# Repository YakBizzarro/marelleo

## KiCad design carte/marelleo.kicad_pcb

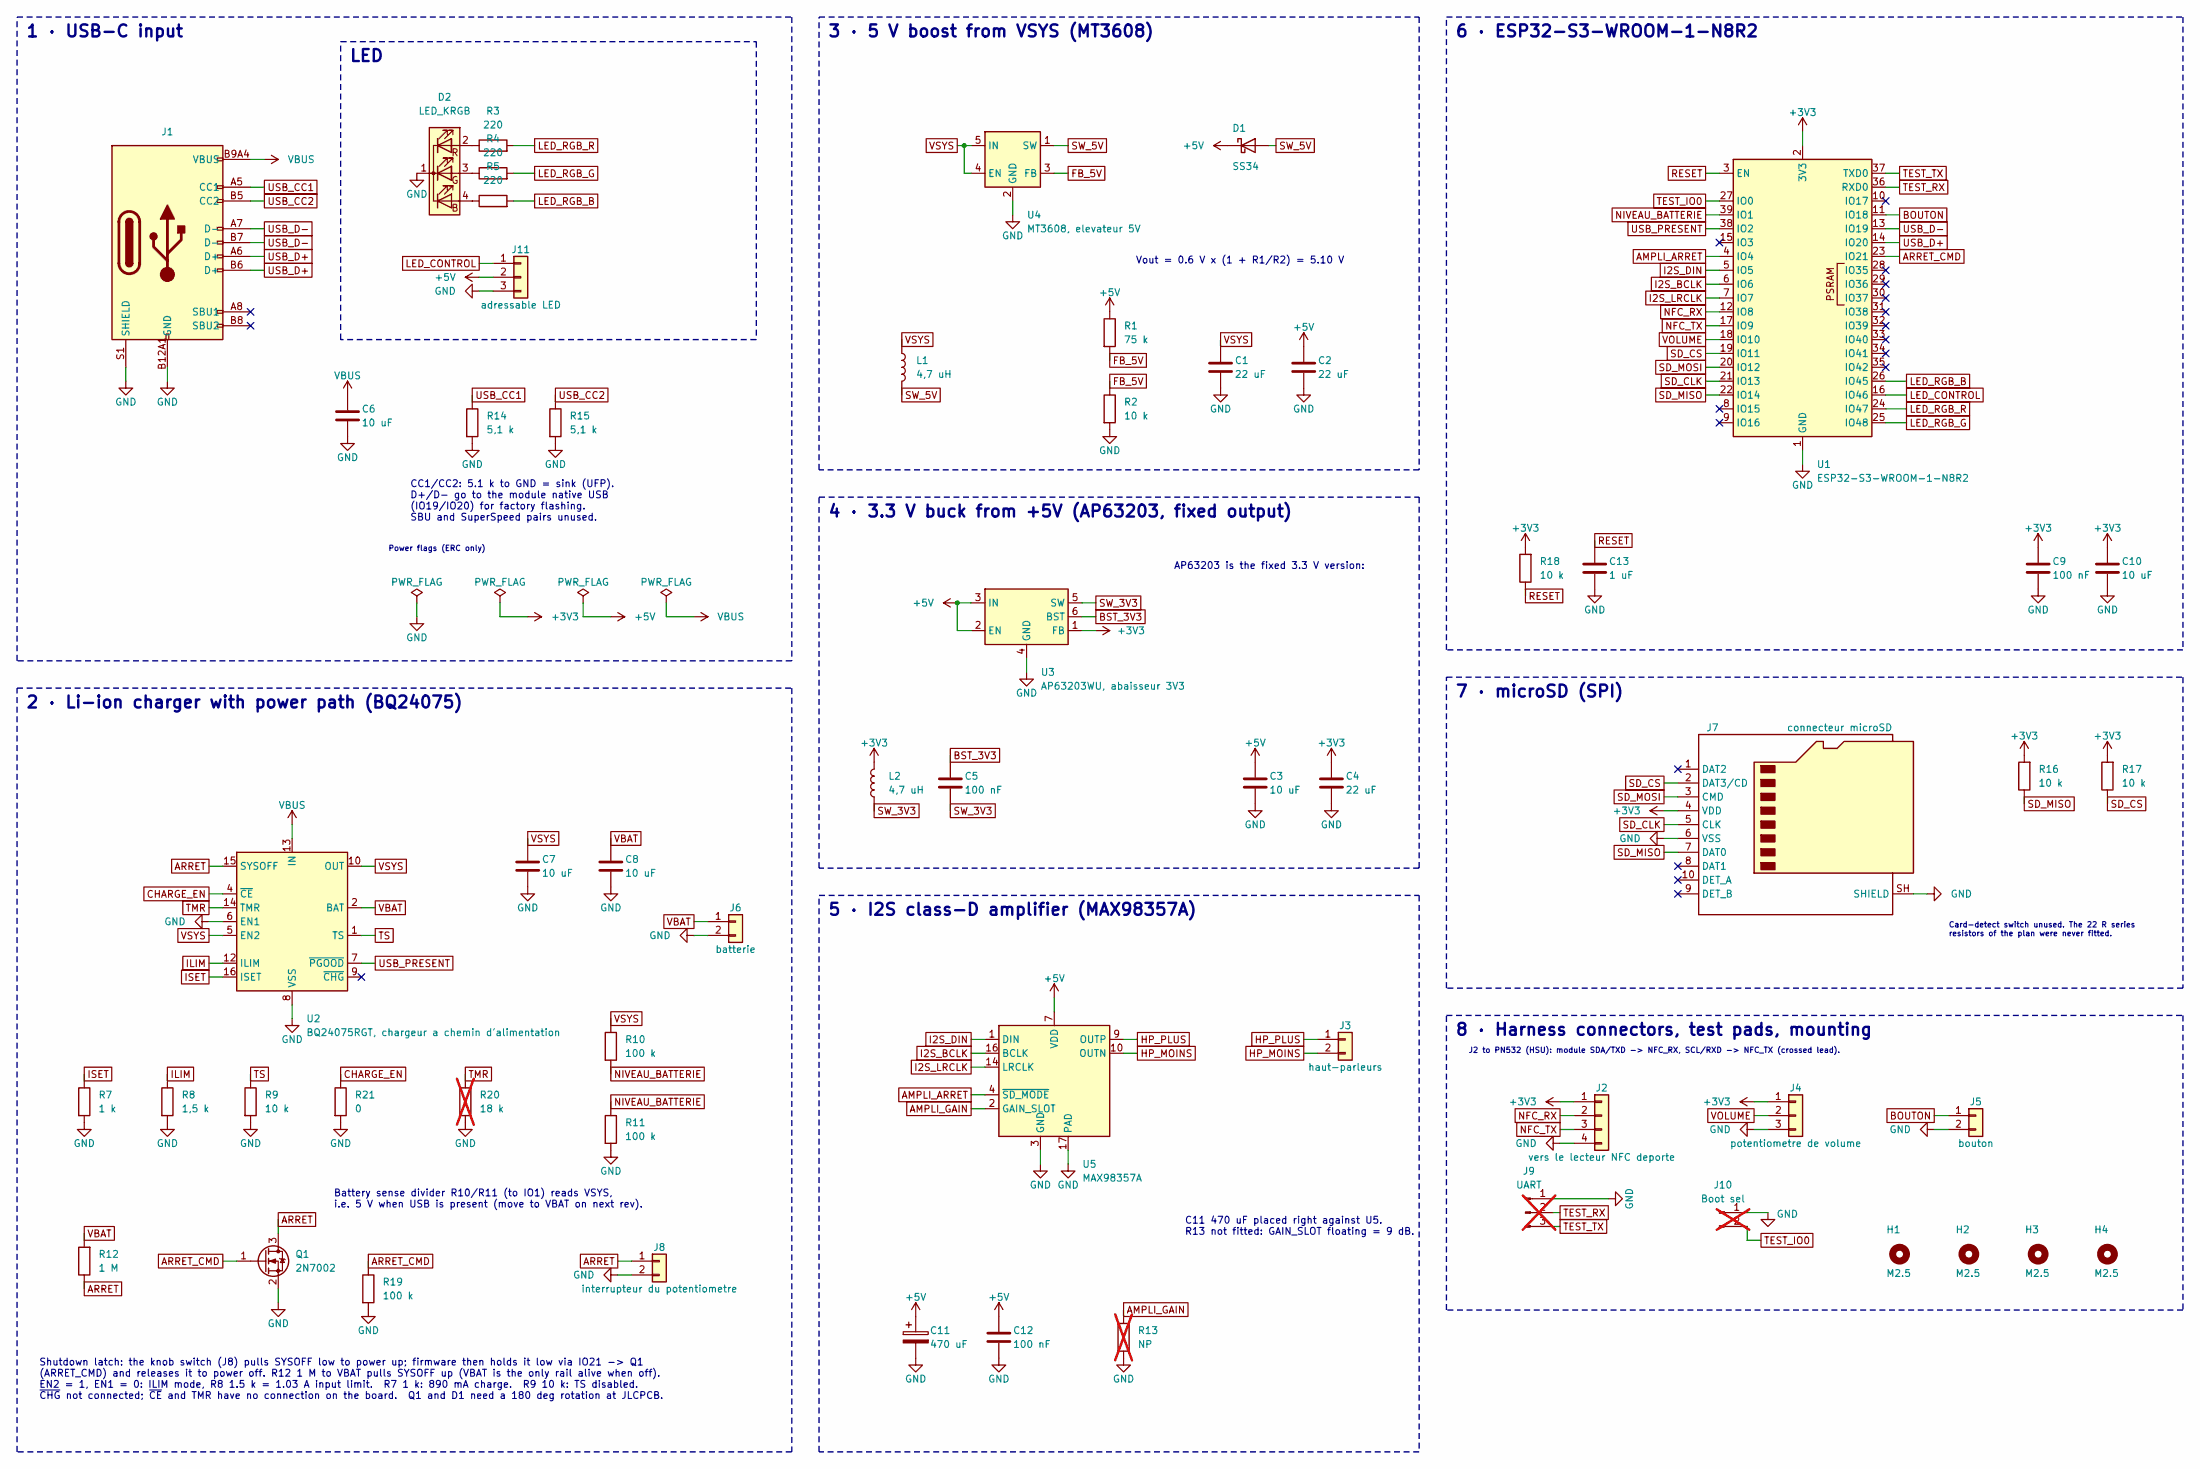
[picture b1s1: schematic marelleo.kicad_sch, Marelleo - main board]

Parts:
C1, C2, C4: 22 uF; C_0805_2012Metric; LCSC C45783
C3, C6, C7, C8, C10: 10 uF; C_0805_2012Metric; LCSC C15850
C5, C9, C12: 100 nF; C_0603_1608Metric; LCSC C14663
C11: 470 uF; CP_Elec_6.3x7.7; LCSC C82004
C13: 1 uF; C_0603_1608Metric; LCSC C15849
D1: SS34; D_SMA; LCSC C8678
D2: LED_KRGB; LED_D5.0mm-4_RGB_Wide_Pins
H1, H2, H3, H4: M2.5; MountingHole_2.7mm_M2.5
J1: Connector, USB-TYPE-C-16P; TYPE-C-SMD_HX-TYPE-C-16PIN; LCSC C2927039
J2: vers le lecteur NFC deporte; JST_PH_S4B-PH-K_1x04_P2.00mm_Horizontal; LCSC C157926
J3: haut-parleurs; JST_PH_S2B-PH-K_1x02_P2.00mm_Horizontal; LCSC C173752
J4: potentiometre de volume; JST_PH_S3B-PH-K_1x03_P2.00mm_Horizontal; LCSC C157929
J5: bouton; JST_PH_S2B-PH-K_1x02_P2.00mm_Horizontal; LCSC C173752
J6: batterie; JST_PH_S2B-PH-K_1x02_P2.00mm_Horizontal; LCSC C173752
J7: connecteur microSD; microSD_HC_Hirose_DM3AT-SF-PEJM5; LCSC C114218
J8: interrupteur du potentiometre; JST_PH_S2B-PH-K_1x02_P2.00mm_Horizontal; LCSC C173752
J9: UART; PinHeader_1x03_P2.54mm_Vertical; not fitted
J10: Boot sel; PinHeader_1x02_P2.54mm_Vertical; not fitted
J11: adressable LED; JST_PH_S3B-PH-K_1x03_P2.00mm_Horizontal; LCSC C157929
L1, L2: 4,7 uH; L_Taiyo-Yuden_MD-4040; LCSC C206284
Q1: 2N7002; SOT-23; LCSC C8545
R1: 75 k; R_0603_1608Metric; LCSC C23242
R2, R9, R16, R17, R18: 10 k; R_0603_1608Metric; LCSC C25804
R3, R4, R5: 220; R_0603_1608Metric
R7: 1 k; R_0603_1608Metric; LCSC C21190
R8: 1,5 k; R_0603_1608Metric; LCSC C22843
R10, R11, R19: 100 k; R_0603_1608Metric; LCSC C25803
R12: 1 M; R_0603_1608Metric; LCSC C22935
R13: NP; R_0603_1608Metric; not fitted
R14, R15: 5,1 k; R_0603_1608Metric; LCSC C23186
R20: 18 k; R_0603_1608Metric; LCSC C25804; not fitted
R21: 0; R_0603_1608Metric; LCSC C25804
U1: ESP32-S3-WROOM-1-N8R2; ESP32-S3-WROOM-1; LCSC C2913204
U2: BQ24075RGT, chargeur a chemin d'alimentation; VQFN-16-1EP_3x3mm_P0.5mm_EP1.1x1.1mm; LCSC C15464
U3: AP63203WU, abaisseur 3V3; TSOT-23-6; LCSC C780769
U4: MT3608, elevateur 5V; SOT-23-6; LCSC C84817
U5: MAX98357A; TQFN-16-1EP_3x3mm_P0.5mm_EP1.23x1.23mm; LCSC C910544

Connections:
+3V3: C4.1, C9.1, C10.1, J2.1, J4.1, J7.4 (VDD), L2.2, R16.2, R17.2, R18.2, U1.2 (3V3), U3.1 (FB)
+5V: C2.1, C3.1, C11.1, C12.1, D1.1 (K), J11.2, R1.1, U3.2 (EN), U3.3 (IN), U5.7 (VDD), U5.8 (VDD)
AMPLI_ARRET: U1.4 (IO4), U5.4 (~SD_MODE)
AMPLI_GAIN: R13.1, U5.2 (GAIN_SLOT)
ARRET: J8.1, Q1.3 (D), R12.1, U2.15 (SYSOFF)
ARRET_CMD: Q1.1 (G), R19.1, U1.23 (IO21)
BOUTON: J5.1, U1.11 (IO18)
BST_3V3: C5.1, U3.6 (BST)
CHARGE_EN: R21.1, U2.4 (~CE)
FB_5V: R1.2, R2.1, U4.3 (FB)
GND: C1.2, C2.2, C3.2, C4.2, C6.2, C7.2, C8.2, C9.2, C10.2, C11.2, C12.2, C13.2, D2.1 (K), J1.A12B1 (GND), J1.B12A1 (GND), J1.S1 (SHIELD), J2.4, J4.3, J5.2, J6.2, J7.6 (VSS), J7.SH (SHIELD), J8.2, J9.1, J10.1, J11.3, Q1.2 (S), R2.2, R7.2, R8.2, R9.2, R11.2, R13.2, R14.2, R15.2, R19.2, R20.2, R21.2, U1.1 (GND), U1.40 (GND), U1.41 (GND), U2.6 (EN1), U2.8 (VSS), U2.17 (VSS), U3.4 (GND), U4.2 (GND), U5.3 (GND), U5.11 (GND), U5.15 (GND), U5.17 (PAD)
HP_MOINS: J3.2, U5.10 (OUTN)
HP_PLUS: J3.1, U5.9 (OUTP)
I2S_BCLK: U1.6 (IO6), U5.16 (BCLK)
I2S_DIN: U1.5 (IO5), U5.1 (DIN)
I2S_LRCLK: U1.7 (IO7), U5.14 (LRCLK)
ILIM: R8.1, U2.12 (ILIM)
ISET: R7.1, U2.16 (ISET)
LED_CONTROL: J11.1, U1.16 (IO46)
LED_RGB_B: R5.2, U1.26 (IO45)
LED_RGB_G: R4.2, U1.25 (IO48)
LED_RGB_R: R3.2, U1.24 (IO47)
NFC_RX: J2.2, U1.12 (IO8)
NFC_TX: J2.3, U1.17 (IO9)
NIVEAU_BATTERIE: R10.2, R11.1, U1.39 (IO1)
unnamed: D2.4 (BA), R5.1
unnamed: D2.3 (GA), R4.1
unnamed: D2.2 (RA), R3.1
RESET: C13.1, R18.1, U1.3 (EN)
SD_CLK: J7.5 (CLK), U1.21 (IO13)
SD_CS: J7.2 (DAT3/CD), R17.1, U1.19 (IO11)
SD_MISO: J7.7 (DAT0), R16.1, U1.22 (IO14)
SD_MOSI: J7.3 (CMD), U1.20 (IO12)
SW_3V3: C5.2, L2.1, U3.5 (SW)
SW_5V: D1.2 (A), L1.2, U4.1 (SW)
TEST_IO0: J10.2, U1.27 (IO0)
TEST_RX: J9.2, U1.36 (RXD0)
TEST_TX: J9.3, U1.37 (TXD0)
TMR: R20.1, U2.14 (TMR)
TS: R9.1, U2.1 (TS)
USB_CC1: J1.A5 (CC1), R14.1
USB_CC2: J1.B5 (CC2), R15.1
USB_D+: J1.A6 (D+), J1.B6 (D+), U1.14 (IO20)
USB_D-: J1.A7 (D-), J1.B7 (D-), U1.13 (IO19)
USB_PRESENT: U1.38 (IO2), U2.7 (~PGOOD)
VBAT: C8.1, J6.1, R12.2, U2.2 (BAT), U2.3 (BAT)
VBUS: C6.1, J1.A9B4 (VBUS), J1.B9A4 (VBUS), U2.13 (IN)
VOLUME: J4.2, U1.18 (IO10)
VSYS: C1.1, C7.1, L1.1, R10.1, U2.5 (EN2), U2.10 (OUT), U2.11 (OUT), U4.4 (EN), U4.5 (IN)

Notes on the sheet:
Battery sense divider R10/R11 (to IO1) reads VSYS, i.e. 5 V when USB is present (move to VBAT on next rev).
Shutdown latch: the knob switch (J8) pulls SYSOFF low to power up; firmware then holds it low via IO21 -> Q1 (ARRET_CMD) and releases it to power off. R12 1 M to VBAT pulls SYSOFF up (VBAT is the only rail alive when off). EN2 = 1, EN1 = 0: ILIM mode, R8 1.5 k = 1.03 A input limit. R7 1 k: 890 mA c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
Card-detect switch unused. The 22 R series resistors of the plan were never fitted.
4 · 3.3 V buck from +5V (AP63203, fixed output)
1 · USB-C input
AP63203 is the fixed 3.3 V version:
3 · 5 V boost from VSYS (MT3608)
CC1/CC2: 5.1 k to GND = sink (UFP). D+/D- go to the module native USB (IO19/IO20) for factory flashing. SBU and SuperSpeed pairs unused.
Power flags (ERC only)
5 · I2S class-D amplifier (MAX98357A)
J2 to PN532 (HSU): module SDA/TXD -> NFC_RX, SCL/RXD -> NFC_TX (crossed lead).
LED
Vout = 0.6 V x (1 + R1/R2) = 5.10 V
6 · ESP32-S3-WROOM-1-N8R2
7 · microSD (SPI)
2 · Li-ion charger with power path (BQ24075)
C11 470 uF placed right against U5. R13 not fitted: GAIN_SLOT floating = 9 dB.
8 · Harness connectors, test pads, mounting

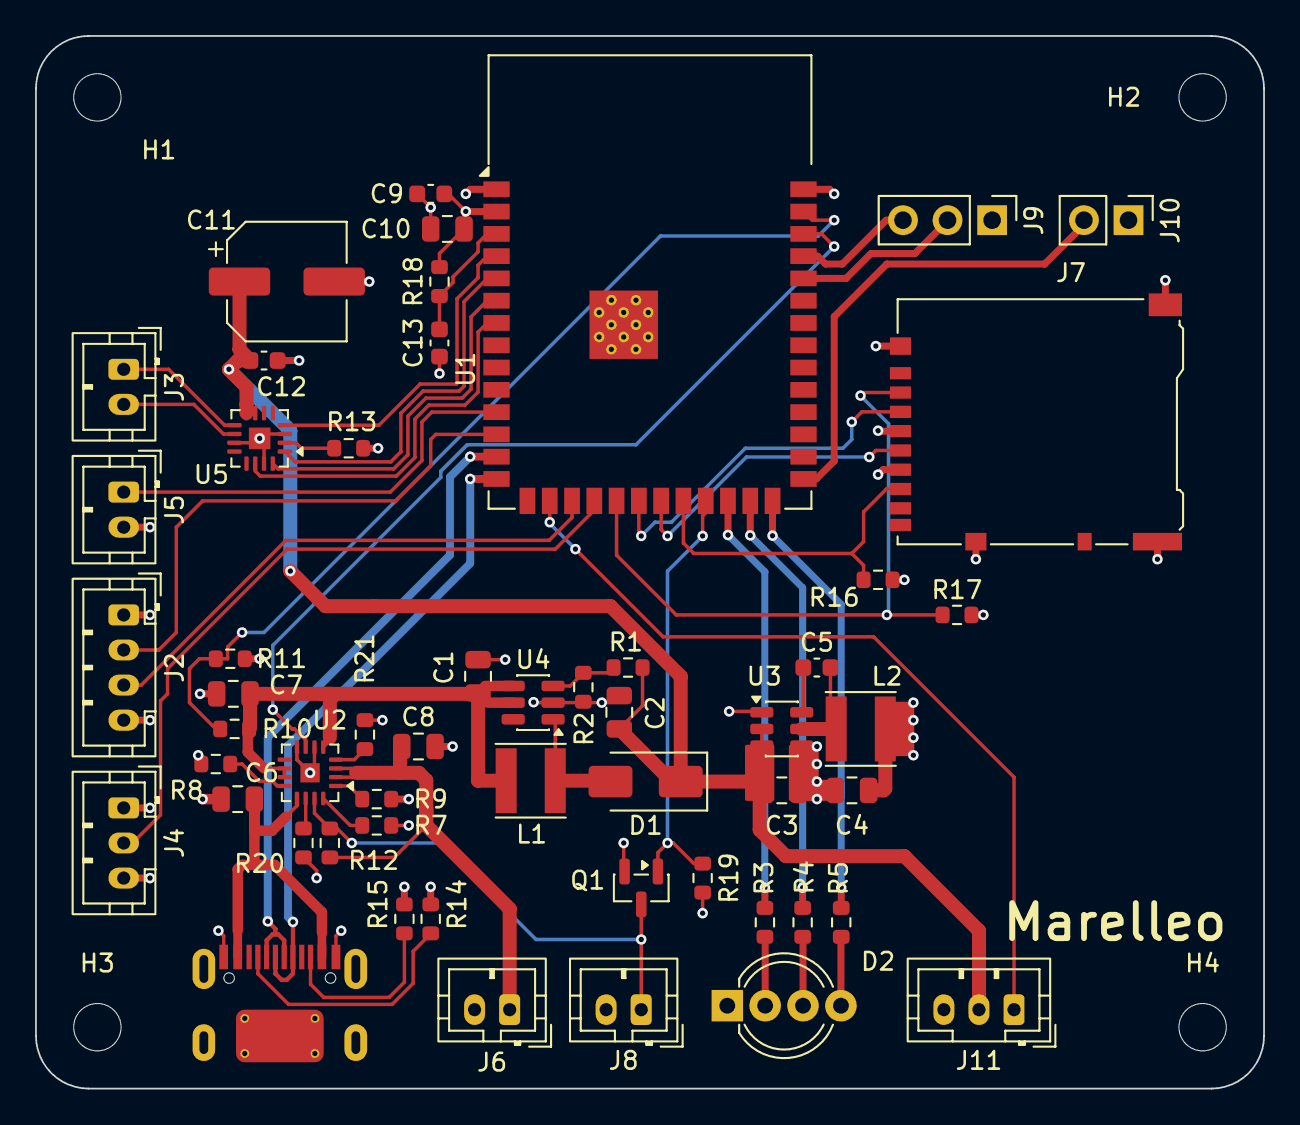
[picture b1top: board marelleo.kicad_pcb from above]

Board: 4 copper layers, 70.0 x 60.0 mm, 58 parts (0 on the bottom side), 49 nets.
